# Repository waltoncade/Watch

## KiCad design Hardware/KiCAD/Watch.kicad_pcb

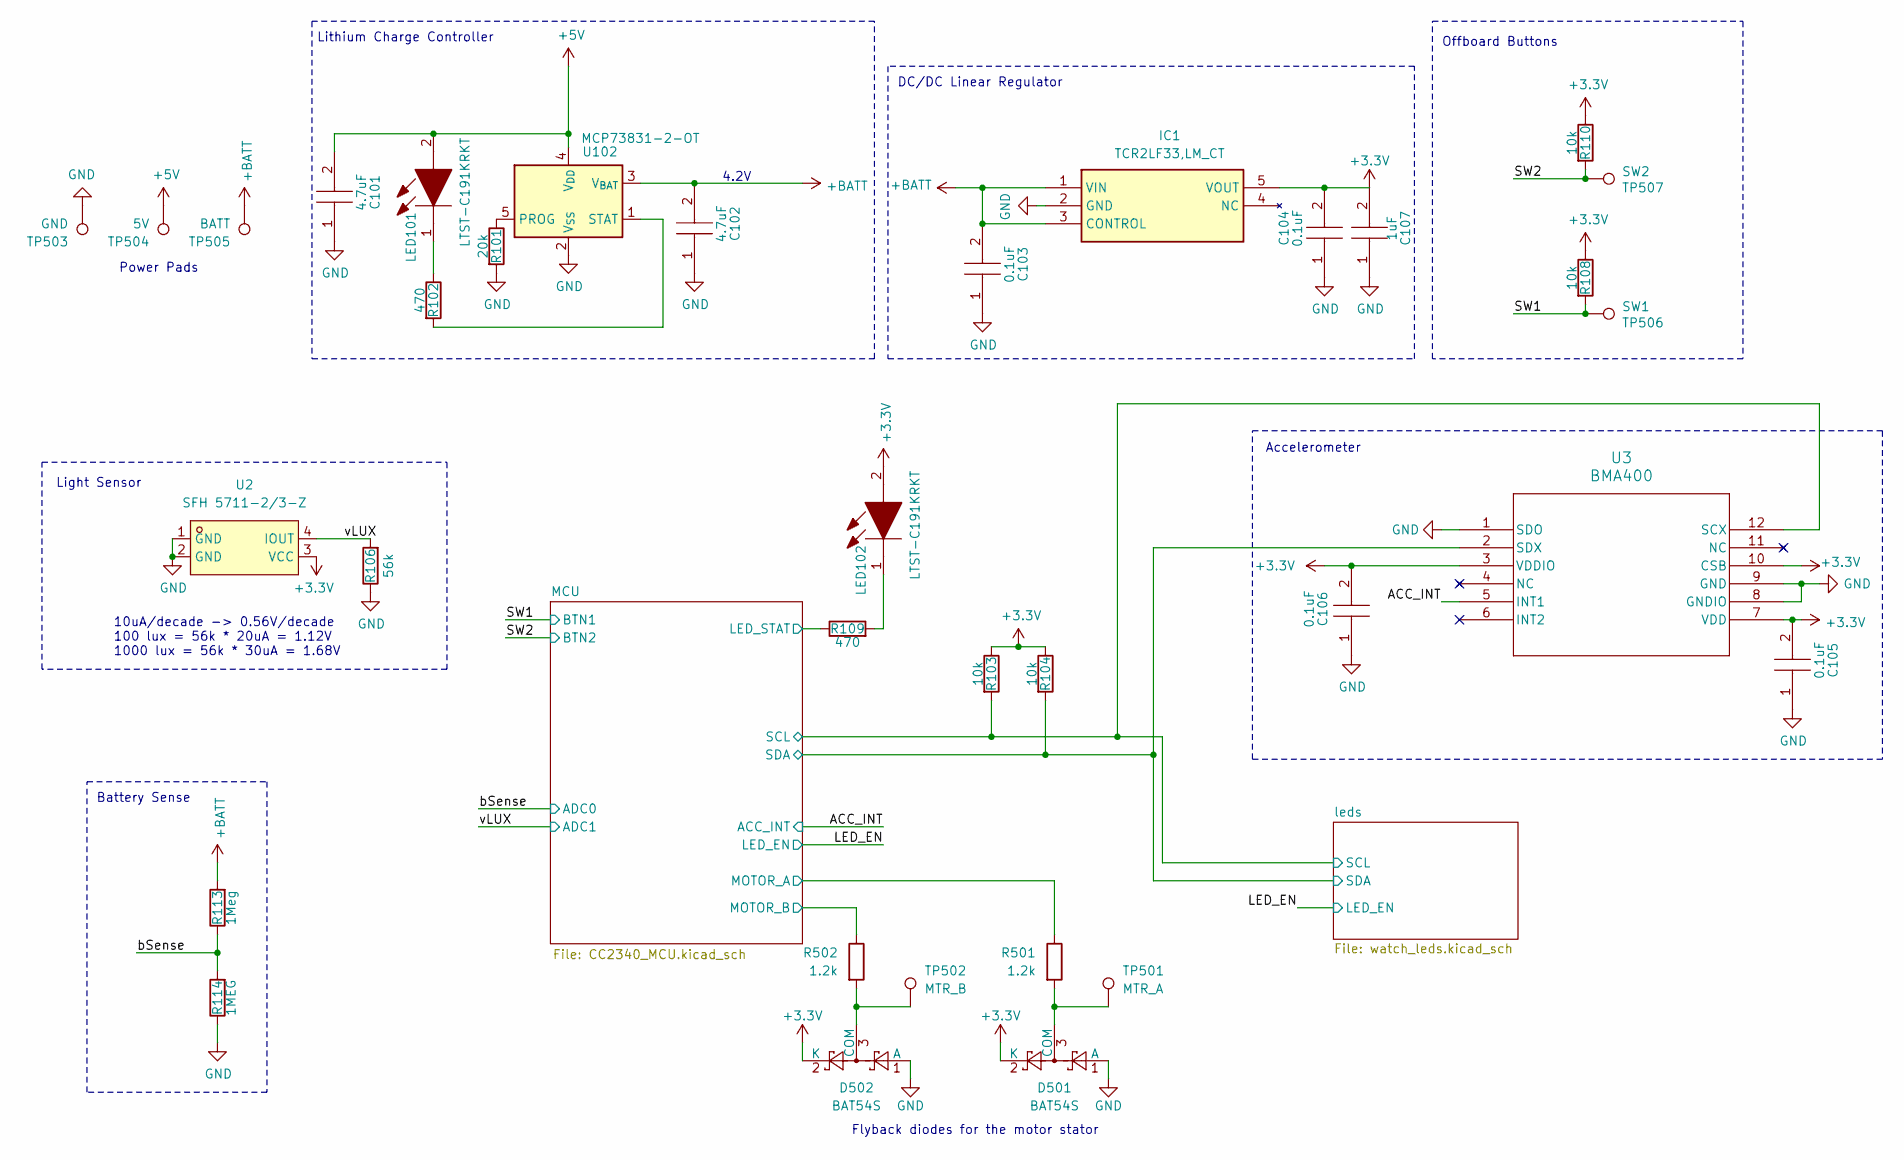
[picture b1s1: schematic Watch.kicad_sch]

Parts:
C101, C102: 4.7uF; CAPC1005X55N; Manufacturer_Part_Number CL05A475MP5NRNC; Mouser Part Number 187-CL05A104KA5NNNC
C103, C104, C105, C106: 0.1uF; CAPC1005X55N; Manufacturer_Part_Number CL05B104KO5NNNC; Mouser Part Number 187-CL05A104KA5NNNC
C107: 1uF; CAPC1005X55N; Manufacturer_Part_Number CL05A105KA5NQNC; LCSC Part C52923
D501, D502: BAT54S; SOT-23; Manufacturer_Part_Number BAT54S,215; LCSC Part C47546
IC1: TCR2LF33,LM_CT; TCR2LF33LMCT; Manufacturer_Part_Number TCR2LF33,LM(CT; Mouser Part Number 757-TCR2LF33LMCT
LED101, LED102: LTST-C191KRKT; LEDC1608X55N; Manufacturer_Part_Number LTST-C191KRKT; Mouser Part Number 859-LTST-C191KRKT
R101: 20k; R_0402_1005Metric; Manufacturer_Part_Number 0402WGF2002TCE; LCSC Part C25765
R102, R109: 470; R_0402_1005Metric; Manufacturer_Part_Number 0402WGF4700TCE; LCSC Part C25117
R103, R104, R108, R110: 10k; R_0402_1005Metric; Manufacturer_Part_Number 0402WGF1002TCE; LCSC Part C25744
R106: 56k; R_0402_1005Metric; Manufacturer_Part_Number 0402WGF5602TCE; LCSC Part C25796
R113: 1Meg; R_0402_1005Metric; Manufacturer_Part_Number 0402WGF1004TCE; LCSC Part C26083
R114: 1MEG; R_0402_1005Metric; Manufacturer_Part_Number 0402WGF1004TCE; LCSC Part C26083
R501, R502: 1.2k; R_0402_1005Metric; Manufacturer_Part_Number 0402WGF1201TCE; LCSC Part C25862
TP501: MTR_A; TestPoint_Pad_D1.5mm
TP502: MTR_B; TestPoint_Pad_D1.5mm
TP503: GND; TestPoint_Pad_D1.5mm
TP504: 5V; TestPoint_Pad_D1.5mm
TP505: BATT; TestPoint_Pad_D1.5mm
TP506: SW1; TestPoint_Pad_D1.5mm
TP507: SW2; TestPoint_Pad_D1.5mm
U2: SFH 5711-2/3-Z; LED-SMD_4P-L2.8-W2.2-FD; MPN SFH 5711-2/3-Z; LCSC Part C2655106
U3: BMA400; QFN_BMA400_BOS-M; Manufacturer_Part_Number BMA400; LCSC Part C437655
U102: MCP73831-2-OT; SOT-23-5; Manufacturer_Part_Number MCP73831T-2ACI/OT; LCSC Part C424093

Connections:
+3.3V: C104.2, C105.2, C106.2, C107.2, D501.2 (K), D502.2 (K), IC1.5 (VOUT), LED102.2, R103.1, R104.1, R108.1, R110.1, U2.3 (VCC), U3.3 (VDDIO), U3.7 (VDD), U3.10 (CSB); also elsewhere on the board
+5V: C101.2, LED101.2, TP504.1, U102.4 (V_{DD})
+BATT: C102.2, C103.2, IC1.1 (VIN), IC1.3 (CONTROL), R113.2, TP505.1, U102.3 (V_{BAT})
/ACC_INT: U3.5 (INT1); also elsewhere on the board
/MCU/LED_STAT: R109.1; also elsewhere on the board
/MCU/MOTOR_A: R501.1; also elsewhere on the board
/MCU/MOTOR_B: R502.1; also elsewhere on the board
/SW1: R108.2, TP506.1; also elsewhere on the board
/SW2: R110.2, TP507.1; also elsewhere on the board
/bSense: R113.1, R114.2; also elsewhere on the board
/leds/SCL: R103.2, U3.12 (SCX); also elsewhere on the board
/leds/SDA: R104.2, U3.2 (SDX); also elsewhere on the board
/vLUX: R106.2, U2.4 (IOUT); also elsewhere on the board
GND: C101.1, C102.1, C103.1, C104.1, C105.1, C106.1, C107.1, D501.1 (A), D502.1 (A), IC1.2 (GND), R101.2, R106.1, R114.1, TP503.1, U2.1 (GND), U2.2 (GND), U3.1 (SDO), U3.8 (GNDIO), U3.9 (GND), U102.2 (V_{SS}); also elsewhere on the board
unnamed: D501.3 (COM), R501.2, TP501.1
unnamed: D502.3 (COM), R502.2, TP502.1
unnamed: LED101.1, R102.1
unnamed: LED102.1, R109.2
unnamed: R101.1, U102.5 (PROG)
unnamed: R102.2, U102.1 (STAT)

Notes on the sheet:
Power Pads
Flyback diodes for the motor stator
4.2V
Battery Sense
Lithium Charge Controller
Offboard Buttons
DC/DC Linear Regulator
Light Sensor
Accelerometer
10uA/decade -> 0.56V/decade 100 lux = 56k * 20uA = 1.12V 1000 lux = 56k * 30uA = 1.68V

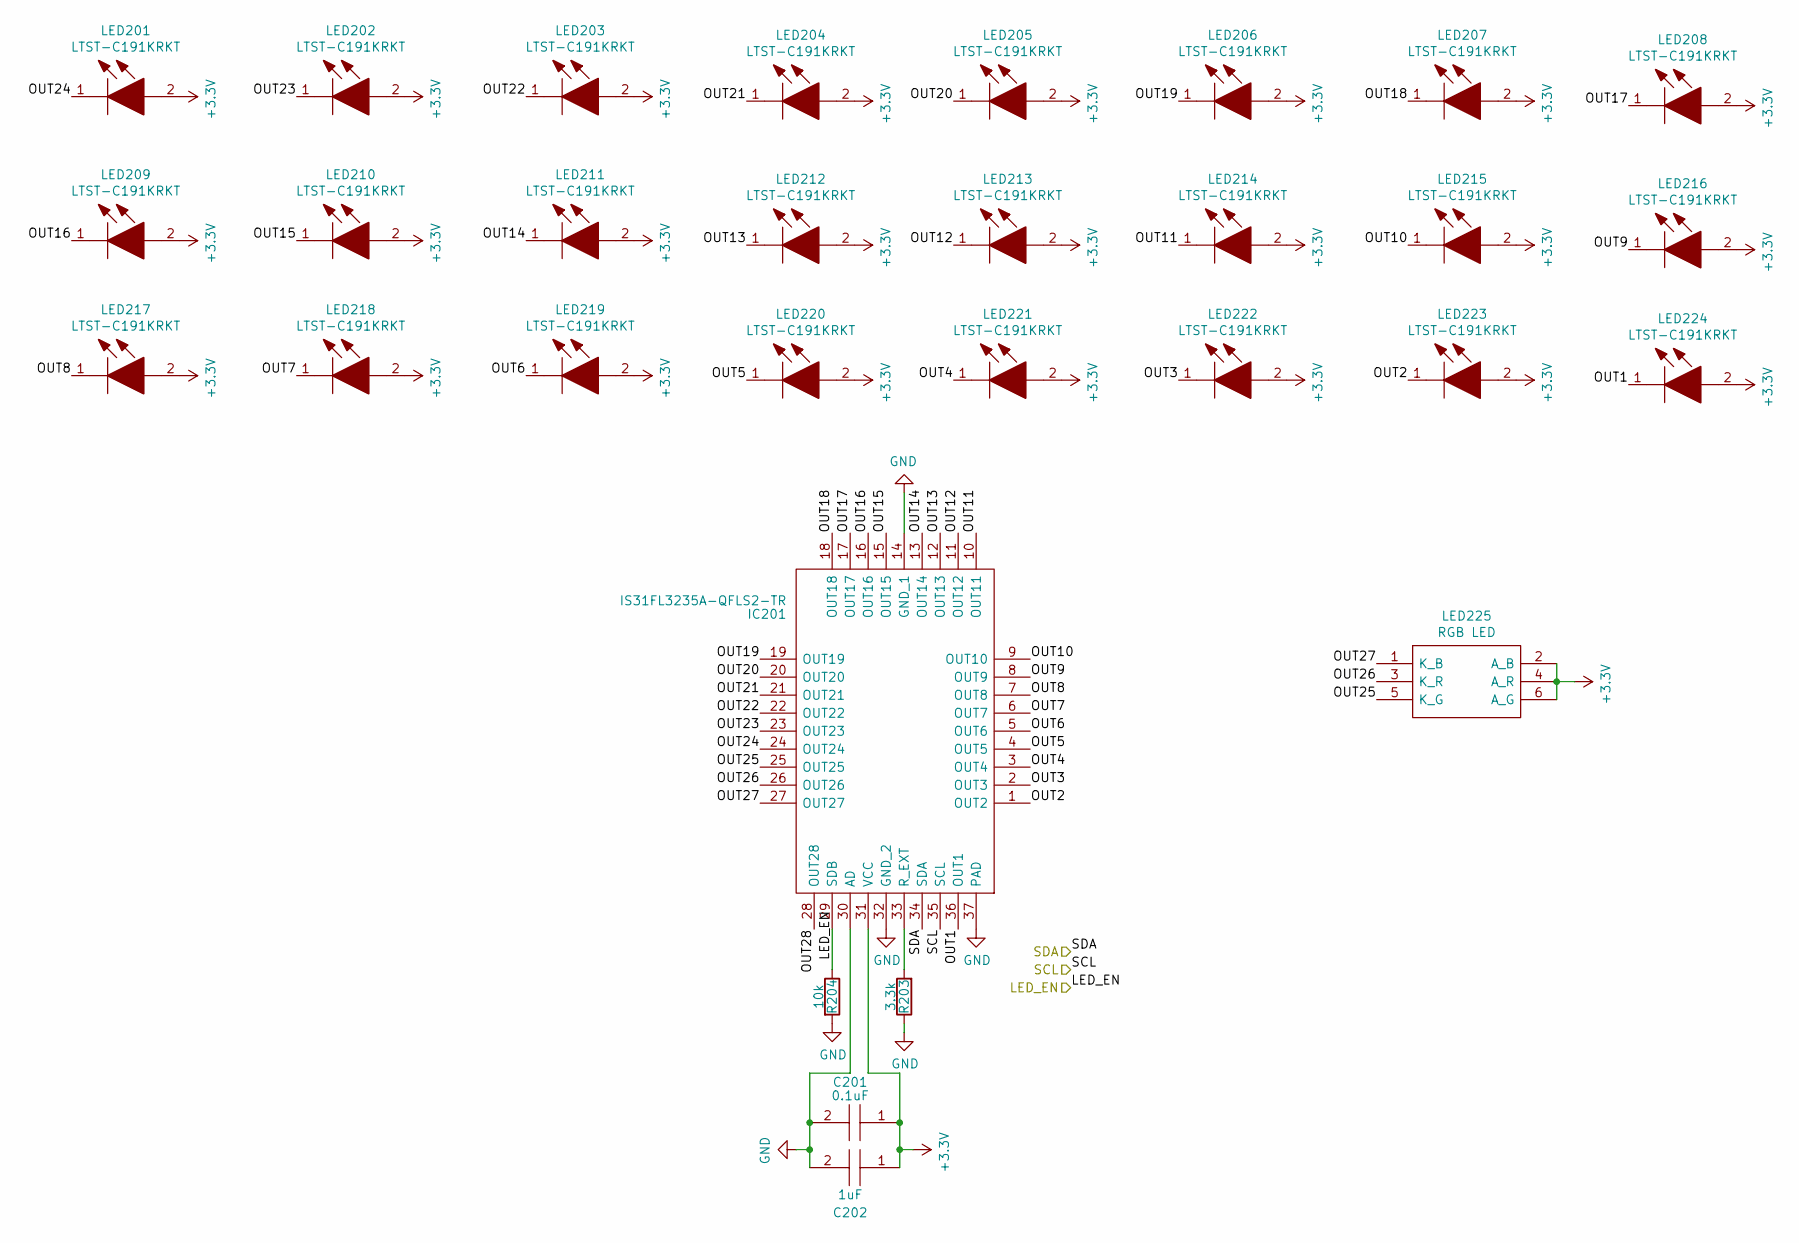
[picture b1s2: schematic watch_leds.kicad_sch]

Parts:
C201: 0.1uF; CAPC1005X55N; Manufacturer_Part_Number CL05B104KO5NNNC; Mouser Part Number 187-CL05A104KA5NNNC
C202: 1uF; CAPC1005X55N; Manufacturer_Part_Number CL05A105KA5NQNC; Mouser Part Number 187-CL05A105KQ5NNNC
IC201: IS31FL3235A-QFLS2-TR; QFN40P400X400X80-37N; Manufacturer_Part_Number IS31FL3235A-QFLS2-TR; Mouser Part Number 870-31FL3235AQFLS2T
LED201, LED202, LED203, LED204, LED205, LED206, LED207, LED208, LED209, LED210, LED211, LED212, LED213, LED214, LED215, LED216, LED217, LED218, LED219, LED220, LED221, LED222, LED223, LED224: LTST-C191KRKT; LEDC1608X55N; Manufacturer_Part_Number LTST-C191KRKT; Mouser Part Number 859-LTST-C191KRKT
LED225: RGB LED; 150352M173300; Mouser Part Number 710-150352M173300
R203: 3.3k; R_0402_1005Metric; Manufacturer_Part_Number 0402WGF3301TCE; LCSC Part C25890
R204: 10k; R_0402_1005Metric; Manufacturer_Part_Number 0402WGF1002TCE; LCSC Part C25744

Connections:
+3.3V: C201.1, C202.1, IC201.31 (VCC), LED201.2, LED202.2, LED203.2, LED204.2, LED205.2, LED206.2, LED207.2, LED208.2, LED209.2, LED210.2, LED211.2, LED212.2, LED213.2, LED214.2, LED215.2, LED216.2, LED217.2, LED218.2, LED219.2, LED220.2, LED221.2, LED222.2, LED223.2, LED224.2, LED225.2 (A_B), LED225.4 (A_R), LED225.6 (A_G); also elsewhere on the board
/LED_EN: IC201.29 (SDB), R204.1; also elsewhere on the board
/leds/OUT1: IC201.36 (OUT1), LED224.1
/leds/OUT2: IC201.1 (OUT2), LED223.1
/leds/OUT3: IC201.2 (OUT3), LED222.1
/leds/OUT4: IC201.3 (OUT4), LED221.1
/leds/OUT5: IC201.4 (OUT5), LED220.1
/leds/OUT6: IC201.5 (OUT6), LED219.1
/leds/OUT7: IC201.6 (OUT7), LED218.1
/leds/OUT8: IC201.7 (OUT8), LED217.1
/leds/OUT9: IC201.8 (OUT9), LED216.1
/leds/OUT10: IC201.9 (OUT10), LED215.1
/leds/OUT11: IC201.10 (OUT11), LED214.1
/leds/OUT12: IC201.11 (OUT12), LED213.1
/leds/OUT13: IC201.12 (OUT13), LED212.1
/leds/OUT14: IC201.13 (OUT14), LED211.1
/leds/OUT15: IC201.15 (OUT15), LED210.1
/leds/OUT16: IC201.16 (OUT16), LED209.1
/leds/OUT17: IC201.17 (OUT17), LED208.1
/leds/OUT18: IC201.18 (OUT18), LED207.1
/leds/OUT19: IC201.19 (OUT19), LED206.1
/leds/OUT20: IC201.20 (OUT20), LED205.1
/leds/OUT21: IC201.21 (OUT21), LED204.1
/leds/OUT22: IC201.22 (OUT22), LED203.1
/leds/OUT23: IC201.23 (OUT23), LED202.1
/leds/OUT24: IC201.24 (OUT24), LED201.1
/leds/OUT25: IC201.25 (OUT25), LED225.5 (K_G)
/leds/OUT26: IC201.26 (OUT26), LED225.3 (K_R)
/leds/OUT27: IC201.27 (OUT27), LED225.1 (K_B)
/leds/OUT28: IC201.28 (OUT28)
/leds/SCL: IC201.35 (SCL); also elsewhere on the board
/leds/SDA: IC201.34 (SDA); also elsewhere on the board
GND: C201.2, C202.2, IC201.14 (GND_1), IC201.30 (AD), IC201.32 (GND_2), IC201.37 (PAD), R203.1, R204.2; also elsewhere on the board
unnamed: IC201.33 (R_EXT), R203.2

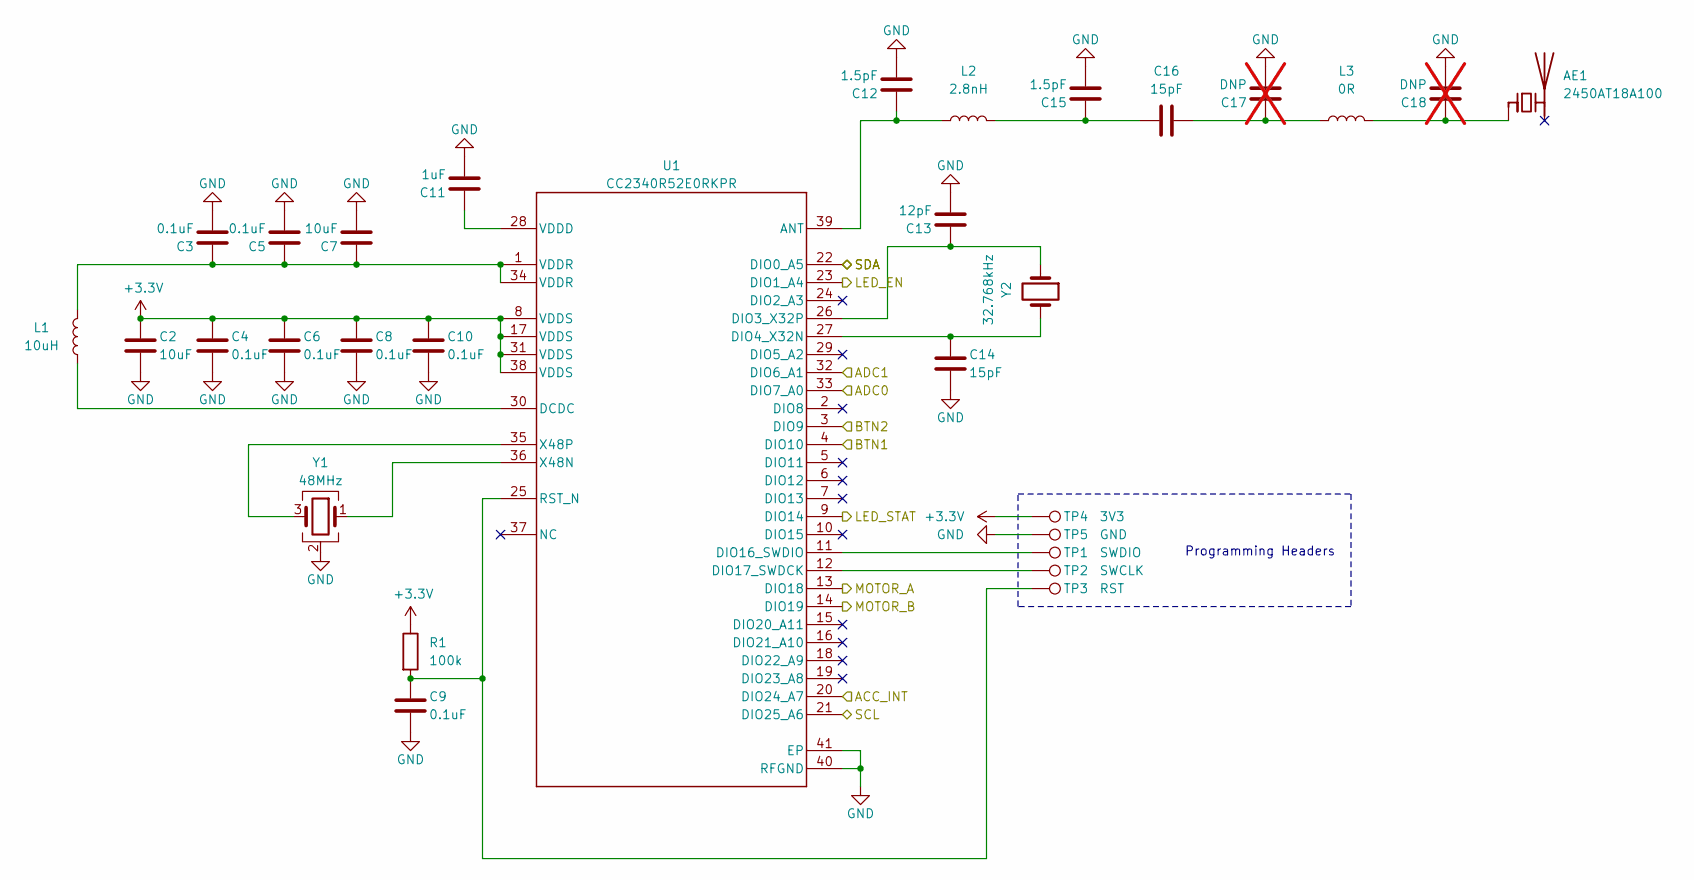
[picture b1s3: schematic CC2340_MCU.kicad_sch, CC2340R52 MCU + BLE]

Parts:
AE1: 2450AT18A100; Johanson_2450AT18x100; MPN Johanson 2450AT18A100 (placeholder, TBD)
C2, C7: 10uF; C_0402_1005Metric; Manufacturer_Part_Number CL05A106MQ5NUNC; LCSC Part C15525
C3, C4, C5, C6, C8, C9, C10: 0.1uF; C_0402_1005Metric; Manufacturer_Part_Number CL05B104KO5NNNC; LCSC Part C1525
C11: 1uF; C_0402_1005Metric; Manufacturer_Part_Number CL05A105KA5NQNC; LCSC Part C52923
C12, C15: 1.5pF; C_0402_1005Metric; Manufacturer_Part_Number 0402CG1R5C500NT; LCSC Part C1552
C13: 12pF; C_0402_1005Metric; Manufacturer_Part_Number 0402CG120J500NT; LCSC Part C1547
C14, C16: 15pF; C_0402_1005Metric; Manufacturer_Part_Number 0402CG150J500NT; LCSC Part C1548
C17, C18: DNP; C_0402_1005Metric; not fitted
L1: 10uH; L_0603_1608Metric; MPN MLZ1608N100LT000; LCSC Part C194437
L2: 2.8nH; L_0402_1005Metric; Manufacturer_Part_Number LQW15AN2N8B00D; LCSC Part C6584793
L3: 0R; L_0402_1005Metric; Manufacturer_Part_Number 0402WGF0000TCE; LCSC Part C17168
R1: 100k; R_0402_1005Metric; Manufacturer_Part_Number 0402WGF1003TCE; LCSC Part C25741
TP1: SWDIO; TestPoint_Pad_D1.0mm
TP2: SWCLK; TestPoint_Pad_D1.0mm
TP3: RST; TestPoint_Pad_D1.0mm
TP4: 3V3; TestPoint_Pad_D1.0mm
TP5: GND; TestPoint_Pad_D1.0mm
U1: CC2340R52E0RKPR; RKP0040B-IPC_B; Manufacturer_Part_Number CC2340R52E0RKPR; LCSC Part C5914214
Y1: 48MHz; Crystal_SMD_2016-4Pin_2.0x1.6mm; MPN NX2016SA-48MHZ-EXS00A-CS05517; LCSC Part C5186571
Y2: 32.768kHz; Crystal_SMD_2012-2Pin_2.0x1.2mm; MPN CM8V-T1A-32.768KHZ-9PF-20PPM-TA-QC; LCSC Part C5142652

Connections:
+3.3V: C2.1, C4.1, C6.1, C8.1, C10.1, R1.1, TP4.1, U1.8 (VDDS), U1.17 (VDDS), U1.31 (VDDS), U1.38 (VDDS); also elsewhere on the board
/ACC_INT: U1.20 (DIO24_A7); also elsewhere on the board
/LED_EN: U1.23 (DIO1_A4); also elsewhere on the board
/MCU/LED_STAT: U1.9 (DIO14); also elsewhere on the board
/MCU/MOTOR_A: U1.13 (DIO18); also elsewhere on the board
/MCU/MOTOR_B: U1.14 (DIO19); also elsewhere on the board
/SW1: U1.4 (DIO10); also elsewhere on the board
/SW2: U1.3 (DIO9); also elsewhere on the board
/bSense: U1.33 (DIO7_A0); also elsewhere on the board
/leds/SCL: U1.21 (DIO25_A6); also elsewhere on the board
/leds/SDA: U1.22 (DIO0_A5); also elsewhere on the board
/vLUX: U1.32 (DIO6_A1); also elsewhere on the board
GND: C2.2, C3.2, C4.2, C5.2, C6.2, C7.2, C8.2, C9.2, C10.2, C11.2, C12.2, C13.2, C14.2, C15.2, C17.2, C18.2, TP5.1, U1.40 (RFGND), U1.41 (EP), Y1.2 (G), Y1.4 (G); also elsewhere on the board
unnamed: AE1.1 (FEED_1), C18.1, L3.2
unnamed: C3.1, C5.1, C7.1, L1.2, U1.1 (VDDR), U1.34 (VDDR)
unnamed: C15.1, C16.1, L2.2
unnamed: C16.2, C17.1, L3.1
unnamed: C12.1, L2.1, U1.39 (ANT)
unnamed: L1.1, U1.30 (DCDC)
unnamed: C13.1, U1.26 (DIO3_X32P), Y2.1
unnamed: C14.1, U1.27 (DIO4_X32N), Y2.2
unnamed: TP1.1, U1.11 (DIO16_SWDIO)
unnamed: TP2.1, U1.12 (DIO17_SWDCK)
unnamed: C9.1, R1.2, TP3.1, U1.25 (RST_N)
unnamed: C11.1, U1.28 (VDDD)
unnamed: U1.36 (X48N), Y1.1
unnamed: U1.35 (X48P), Y1.3

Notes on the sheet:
Programming Headers

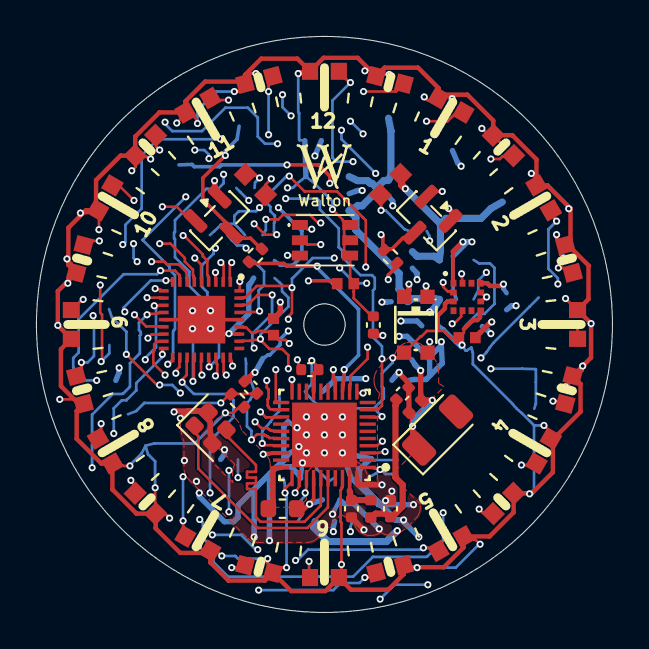
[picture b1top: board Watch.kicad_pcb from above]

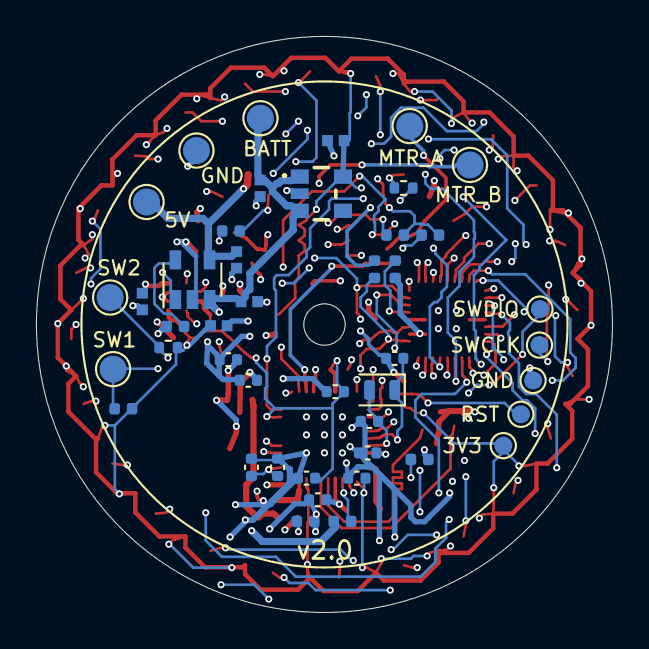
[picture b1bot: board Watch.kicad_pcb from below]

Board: 4 copper layers, 32.0 x 32.0 mm, 96 parts (44 on the bottom side), 63 nets.

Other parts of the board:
H1: Hand shaft 2.3mm NPTH; NPTH_2.0mm_HandShaft
LOGO1: W_Logo

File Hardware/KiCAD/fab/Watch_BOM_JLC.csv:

Comment,Designator,Footprint,LCSC Part #
2450AT18A100,AE1,Johanson_2450AT18x100,
10uF,"C2,C7",C_0402_1005Metric,
0.1uF,"C3,C4,C5,C6,C8,C9,C10",C_0402_1005Metric,
1uF,C11,C_0402_1005Metric,
1.5pF,"C12,C15",C_0402_1005Metric,
12pF,C13,C_0402_1005Metric,
15pF,"C14,C16",C_0402_1005Metric,
TBD,"C17,C18",C_0402_1005Metric,
4.7uF,"C101,C102",CAPC1005X55N,
0.1uF,"C103,C104,C105,C106,C201",CAPC1005X55N,
1uF,C107,CAPC1005X55N,C52923
1uF,C202,CAPC1005X55N,
BAT54S,"D501,D502",SOT-23,
"TCR2LF33,LM_CT",IC1,TCR2LF33LMCT,
IS31FL3235A-QFLS2-TR,IC201,QFN40P400X400X80-37N,
10uH,L1,L_0603_1608Metric,
2.8nH,L2,L_0402_1005Metric,
TBD,L3,L_0402_1005Metric,
LTST-C191KRKT,"LED101,LED102,LED201,LED202,LED203,LED204,LED205,LED206,LED207,LED208,LED209,LED210,LED211,LED212,LED213,LED214,LED215,LED216,LED217,LED218,LED219,LED220,LED221,LED222,LED223,LED224",LEDC1608X55N,
RGB LED,LED225,150352M173300,
100k,R1,R_0402_1005Metric,
20k,R101,R_0402_1005Metric,C25765
470,"R102,R109",R_0402_1005Metric,
10k,"R103,R104,R108,R110,R204",R_0402_1005Metric,
56k,R106,R_0402_1005Metric,
1M,"R113,R114",R_0402_1005Metric,
3.3k,R203,R_0402_1005Metric,
1.2k,"R501,R502",R_0402_1005Metric,
CC2340R52E0RKPR,U1,RKP0040B-IPC_B,
SFH 5711-2/3-Z,U2,LED-SMD_4P-L2.8-W2.2-FD,C2655106
BMA400,U3,QFN_BMA400_BOS-M,
MCP73831-2-OT,U102,SOT-23-5,
48MHz,Y1,Crystal_SMD_2016-4Pin_2.0x1.6mm,
32.768kHz,Y2,Crystal_SMD_2012-2Pin_2.0x1.2mm,

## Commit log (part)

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2021-11-15 Initial Commit, Directory Structure
2021-11-16 Firmware Init
2022-05-05 MCU and PCB cutout complete, ring of lights pattern placed
2022-05-12 Light driver schematic layout complete
2022-06-02 Wireless charging init
2022-06-22 LTSpice zener diode tests. Watch HW now has lipo charger IC and RGB LED for status monitoring
2022-07-01 Hardware mounting aligned. Dimensions set.
2022-07-12 Finalizing watch hardware
2023-02-19 Parnis Config
2023-02-19 Omega layout and silkscreen complete!
2023-03-20 Added various necessary circuits such as light sensor, button pads, RTC cleanup.
2023-04-02 First Schematic layout complete
2023-04-03 Layout almost complete, hitting some snags with routing LED driver
2023-04-04 Signals routed. Ground pours in progress
2023-04-08 Layout complete, pending inspection and purchase
2023-04-16 Release v1.0
2023-11-11 Light flashing!
2023-12-01 Some reason broken?
2023-12-01 Light blinking :)
2023-12-01 Cleanup!
2023-12-01 More buildz
2023-12-01 Debug gone
2023-12-01 Gitignore builds
2023-12-01 Ignore for real
